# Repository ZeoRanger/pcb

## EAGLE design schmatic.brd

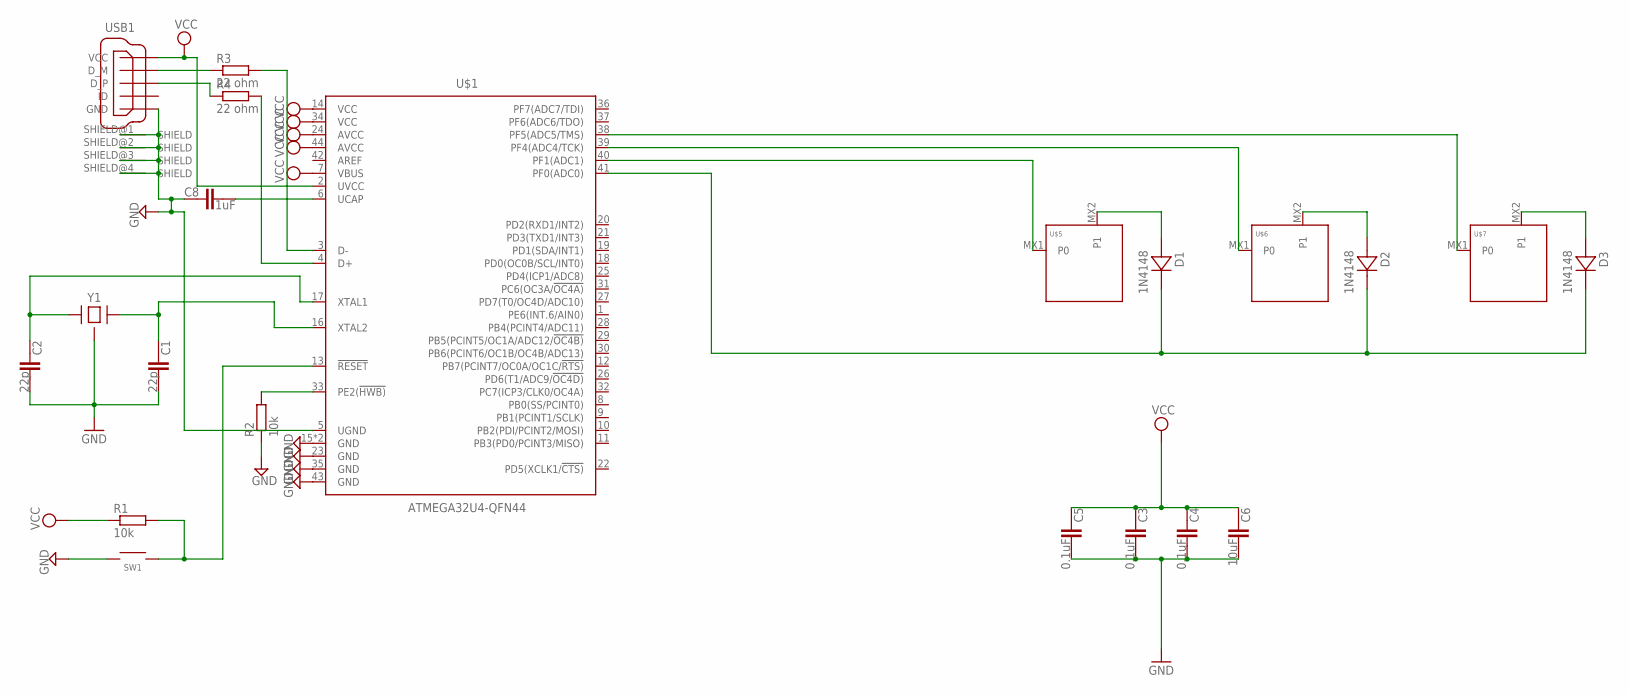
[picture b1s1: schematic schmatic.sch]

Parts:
C1, C2: 22p; C0402
C3, C4, C5: 0.1uF; C0402
C6: 10uF; C0402
C8: 1uF; C0402
D1, D2, D3: 1N4148; DO-35
R1, R2: 10k; R0402
R3, R4: 22 ohm; R0402
SW1: SWITCH-SMD-EVQP-P2602W
U$1: ATMEGA32U4-QFN44; QFN-44
U$5, U$6, U$7: KEYSWITCH-PLAIN-MXHSPCB-1U; MXHSPCB-1U
USB1: USB_CONN-MICRO-FEMALE; ZB62D-B-5PA8
Y1: CRYSTAL-4PIN-3.2X2.5; CRYSTAL-3.2X2.5

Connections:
GND: C1.2, C2.2, C3.2, C4.2, C5.2, C6.2, C8.1, R2.1, SW1.1A (1), SW1.1B (1), U$1.5 (UGND), U$1.15 (GND), U$1.23 (GND), U$1.35 (GND), U$1.43 (GND), U$1.TAB (GND), USB1.5 (GND), USB1.SHIELD@1 (SHIELD), USB1.SHIELD@2 (SHIELD), USB1.SHIELD@3 (SHIELD), USB1.SHIELD@4 (SHIELD), Y1.2 (GND), Y1.4 (GND)
unnamed: C2.1, U$1.17 (XTAL1), Y1.1
unnamed: C1.1, U$1.16 (XTAL2), Y1.3 (2)
unnamed: R1.2, SW1.2A (2), SW1.2B (2), U$1.13 (!RESET)
unnamed: R2.2, U$1.33 (PE2(!HWB))
unnamed: R3.1, USB1.2 (D_M)
unnamed: R3.2, U$1.3 (D-)
unnamed: R4.2, U$1.4 (D+)
unnamed: R4.1, USB1.3 (D_P)
unnamed: U$1.39 (PF4(ADC4/TCK)), U$6.MX1 (P0)
unnamed: C8.2, U$1.6 (UCAP)
unnamed: D1.C, D2.C, D3.C, U$1.41 (PF0(ADC0))
unnamed: U$1.40 (PF1(ADC1)), U$5.MX1 (P0)
unnamed: U$1.38 (PF5(ADC5/TMS)), U$7.MX1 (P0)
unnamed: D1.A, U$5.MX2 (P1)
unnamed: D2.A, U$6.MX2 (P1)
unnamed: D3.A, U$7.MX2 (P1)
VCC: C3.1, C4.1, C5.1, C6.1, R1.1, U$1.2 (UVCC), U$1.7 (VBUS), U$1.14 (VCC), U$1.24 (AVCC), U$1.34 (VCC), U$1.44 (AVCC), USB1.1 (VCC)

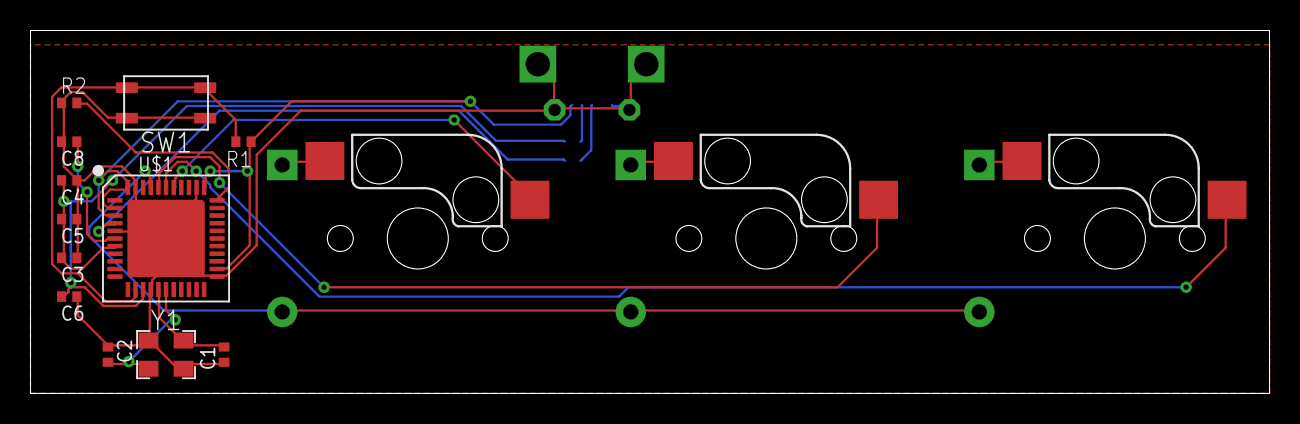
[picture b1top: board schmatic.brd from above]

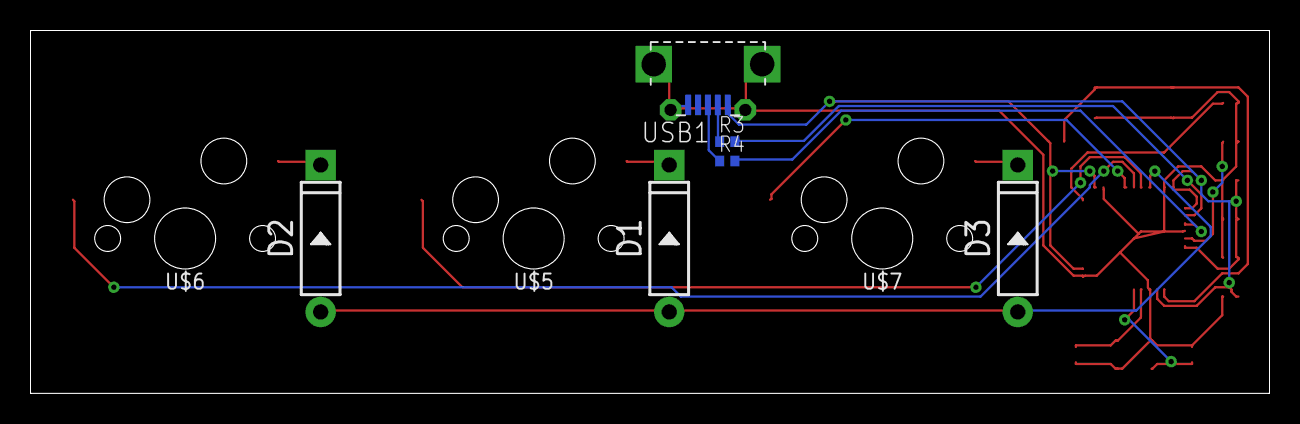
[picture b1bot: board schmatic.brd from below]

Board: 2 copper layers, 81.3 x 23.8 mm, 21 parts (6 on the bottom side), 18 nets.

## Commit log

2020-04-06 init
    adding eagle schematic and board and png photos of both
2020-04-08 updated based off feedback, included extra osh screenshot
